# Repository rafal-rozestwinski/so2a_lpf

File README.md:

# Low Pass Filter PCB

## Instructions

Use only NPO/C0G capacitors. Note the voltage rating. I'm using only 1206/0805 C0G 1kV capacitors.

Photos of results measured with NanoVNA are in /img directory.

Amidon/Micrometals toroids (material 2 and 6) should work out of the box. Alternatives may work too, try them and measure with NanoVNA.

## lpf_qrplabs_3inductors

Use values from https://qrp-labs.com/lpfkit.html

## lpf_2inductors

Use values from http://www.profimot.pl/sp2fp/LPF_HF_50wat/LPF_HF_50wat_sp2fp.html

## lpfserialresonance1 and bs170driver_with_series_resonance_lpf

5-6W at lower bands; 2-3W at 10m. Should be driven by 74ACT00 gate for full power.

Use values from (tr)uSDX project, e.g. https://dl2man.de/wp-content/uploads/2022/10/truSDX_Main-RF_Boards_with_Notes_v1.0n.pdf

Note: for some reason, T37-X cores work better than T50-X (with the same inductance) - reason unknown, but this forces using smaller copper wire.

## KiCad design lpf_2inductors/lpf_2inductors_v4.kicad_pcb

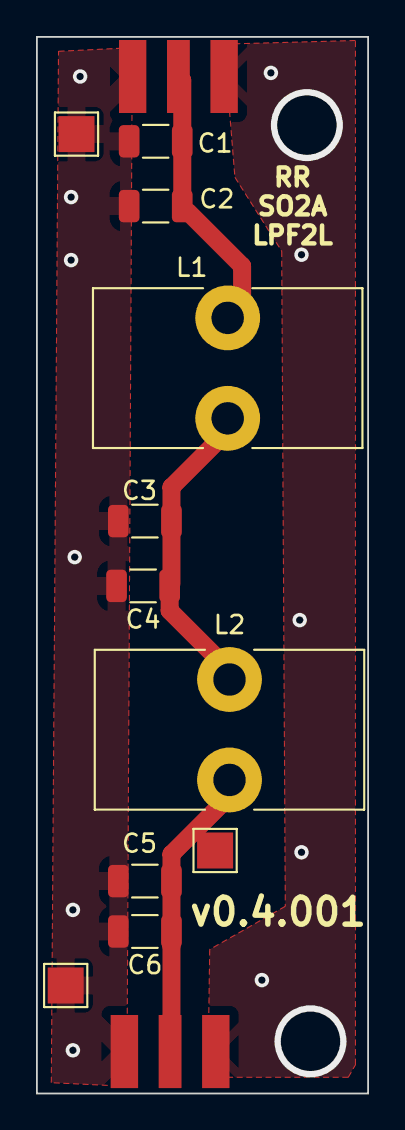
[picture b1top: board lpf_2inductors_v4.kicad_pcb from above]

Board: 2 copper layers, 18.4 x 58.7 mm, 10 parts (0 on the bottom side), 3 nets.

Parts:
C1, C2, C3, C4, C5, C6: C; C_1206_3216Metric
L1, L2: INDUCTOR; L_Toroid_Vertical_L14.7mm_W8.6mm_P5.58mm_Pulse_KM-1
SMA1, SMA1#2: SMA; SMA_EDGELAUNCH_Modded

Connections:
GND: C1.1, C2.1, C3.2, C4.2, C5.2, C6.2, SMA1.2, SMA1#2.2
unnamed: C1.2, C2.2, C3.1, C4.1, L1.1, L1.2, L2.1, SMA1.1
unnamed: C5.1, C6.1, L2.2, SMA1#2.1

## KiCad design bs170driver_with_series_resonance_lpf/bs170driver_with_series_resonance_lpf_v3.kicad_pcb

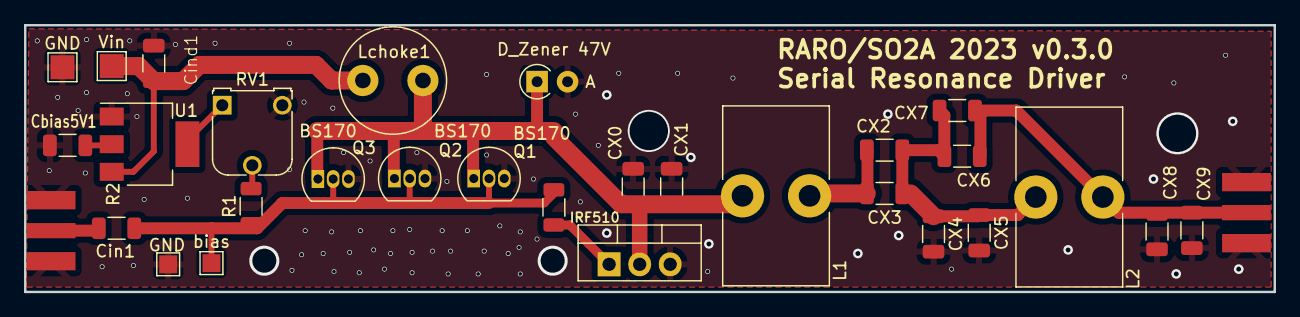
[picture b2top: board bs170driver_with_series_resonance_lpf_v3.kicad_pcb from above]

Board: 2 copper layers, 104.0 x 22.2 mm, 31 parts (0 on the bottom side), 11 nets.

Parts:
CX0, CX1, CX2, CX3, CX4, CX5, CX6, CX7, CX8, CX9: C; C_1206_3216Metric
Cbias5V1: C; C_1206_3216Metric
Cin1: C; C_1206_3216Metric
Cind1: C; C_1206_3216Metric
D1: D_Zener 47V; D_A-405_P2.54mm_Vertical_AnodeUp
GND: TestPoint_Pad_1.5x1.5mm
GND#2: TestPoint_Pad_2.0x2.0mm
IRF510: IRF540N; TO-220-3_Vertical
L1, L2: L; L_Toroid_Vertical_L14.7mm_W8.6mm_P5.58mm_Pulse_KM-1
Lchoke1: L; L_Radial_D8.7mm_P5.00mm_Fastron_07HCP
Q1, Q2, Q3: BS170; TO-92_Inline
R1, R2: R; R_1206_3216Metric
RV1: R_Potentiometer; Potentiometer_Runtron_RM-065_Vertical
SMA1, SMA1#2: SMA; SMA_EDGELAUNCH_Modded
U1: LM1117MP-5.0; SOT-223-3_TabPin2
Vin: TestPoint_Pad_2.0x2.0mm
bias: TestPoint_Pad_1.5x1.5mm

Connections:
/LpfInternal1: CX2.1, CX3.2, CX4.1, CX5.1, CX6.2, CX7.2, L2.1
/Output: CX6.1, CX7.1, CX8.1, CX9.1, L2.2, SMA1#2.1
/afterL1BeforeLpf: CX2.2, CX3.1, L1.2
/choke_vin: Cind1.1, Lchoke1.1, U1.3 (VI), Vin.1
/rfIn: Cin1.1, SMA1.1
GND: CX0.2, CX1.2, CX4.2, CX5.2, CX8.2, CX9.2, Cbias5V1.1, Cind1.2, D1.2 (A), GND.1, GND#2.1, IRF510.3 (S), Q1.3 (S), Q2.3 (S), Q3.3 (S), RV1.3, SMA1.2, SMA1#2.2, U1.1 (GND)
unnamed: CX0.1, CX1.1, D1.1 (K), IRF510.2 (D), L1.1, Lchoke1.2, Q1.1 (D), Q2.1 (D), Q3.1 (D)
unnamed: Cin1.2, Q1.2 (G), Q2.2 (G), Q3.2 (G), R1.1, R2.1, bias.1
unnamed: IRF510.1 (G), R2.2
unnamed: R1.2, RV1.2
unnamed: Cbias5V1.2, RV1.1, U1.2 (VO)

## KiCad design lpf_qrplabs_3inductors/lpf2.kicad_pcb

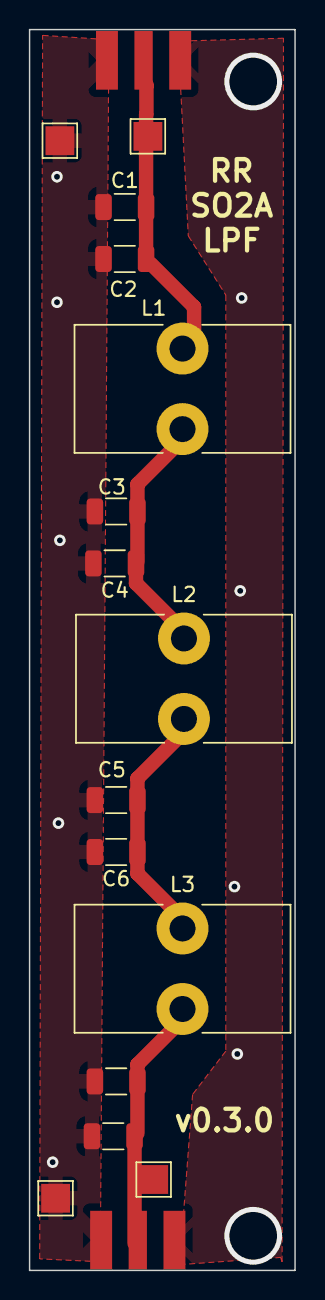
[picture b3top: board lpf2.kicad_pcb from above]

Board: 2 copper layers, 18.4 x 86.0 mm, 13 parts (0 on the bottom side), 4 nets.

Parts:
C1, C2, C3, C4, C5, C6, C7, C8: C; C_1206_3216Metric
L1, L2, L3: INDUCTOR; L_Toroid_Vertical_L14.7mm_W8.6mm_P5.58mm_Pulse_KM-1
SMA1, SMA1#2: SMA; SMA_EDGELAUNCH_Modded

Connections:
GND: C1.1, C2.1, C3.2, C4.2, C5.2, C6.2, C7.2, C8.2, SMA1.2, SMA1#2.2
unnamed: C1.2, C2.2, C3.1, C4.1, L1.1, L1.2, L2.1, SMA1.1
unnamed: C5.1, C6.1, L2.2, L3.1
unnamed: C7.1, C8.1, L3.2, SMA1#2.1

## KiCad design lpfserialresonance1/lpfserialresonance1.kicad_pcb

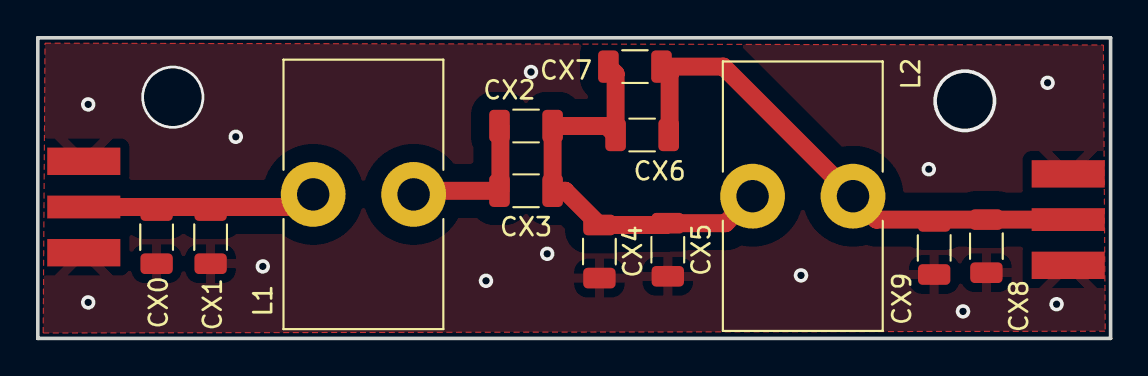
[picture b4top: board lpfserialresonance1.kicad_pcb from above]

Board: 2 copper layers, 59.6 x 16.7 mm, 14 parts (0 on the bottom side), 4 nets.

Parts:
CX0, CX1, CX2, CX3, CX4, CX5, CX6, CX7, CX8, CX9: C; C_1206_3216Metric
L1, L2: L; L_Toroid_Vertical_L14.7mm_W8.6mm_P5.58mm_Pulse_KM-1
SMA1, SMA1#2: SMA; SMA_EDGELAUNCH_Modded

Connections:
GND: CX0.2, CX1.2, CX4.2, CX5.2, CX8.2, CX9.1, SMA1.2, SMA1#2.2
unnamed: CX0.1, CX1.1, L1.1, SMA1.1
unnamed: CX2.1, CX3.2, CX4.1, CX5.1, CX6.2, CX7.2, L2.1
unnamed: CX2.2, CX3.1, CX6.1, CX7.1, CX8.1, CX9.2, L1.2, L2.2, SMA1#2.1

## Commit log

2023-09-26 initial
